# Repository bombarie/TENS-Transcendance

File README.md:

# TENS-Transcendance

Hardware design and code related to the development of a remotely-triggerable system of TENS muscle stimulation as part of the experimental dance / VR performance [Transcendance](https://www.theaterutrecht.nl/voorstellingen/transcendance).

The system extends an existing TENS muscle stimulator, the [Promed TENS 1000S](https://www.promed.de/soft-therapy/electrical-pain-therapy/144/promed-pain-therapy-device-tens-1000-s) and makes it controllable with OpenSoundControl (OSC) via WiFi through the use of an ESP32 microcontroller.

### Included in this repository 

**Software**
  - The [Arduino](https://www.arduino.cc/) code for the ESP32 microcontroller.
  - The code for the [Processing](https://processing.org/) sketch which served as a proxy between the ESP32 and a [TouchDesigner](https://derivative.ca/) patch (not by me) that was heavily integrating most of the performance.

**Hardware**
- The hardware designs to split a single TENS output channel to up to 16 different target locations. The PCB was designed in [KiCad](https://www.kicad.org/) 6.0.
- The additional libraries used in KiCad while designing the PCB are included in the repository.

### Dependencies

The software dependencies are enumerated in the Arduino and Processing folders.

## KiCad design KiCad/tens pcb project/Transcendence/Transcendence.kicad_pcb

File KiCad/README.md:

# KiCad designs

For this project we used a [Promed TENS 1000S](https://www.promed.de/soft-therapy/electrical-pain-therapy/144/promed-pain-therapy-device-tens-1000-s) TENS muscle stimulator, however there was a need to create multiple outputs, with these not needing to be active simultaneously. The TENS Output Board was designed in KiCad 6.x to support this use case. It houses a [CD74HC4067 16-channel multiplexer](https://www.sparkfun.com/products/9056) board and the switching is done using [Vishay VOR1142A6](https://www.digikey.com/en/products/detail/vishay-semiconductor-opto-division/VOR1142A6/6174564) mosfet relays.

Pressed for time the board was designed with ample room for further miniaturisation. Using solely through-hole components and spaced widely it has a distinctly oldschool look which I don't hate :)

### board layout

### 3d preview

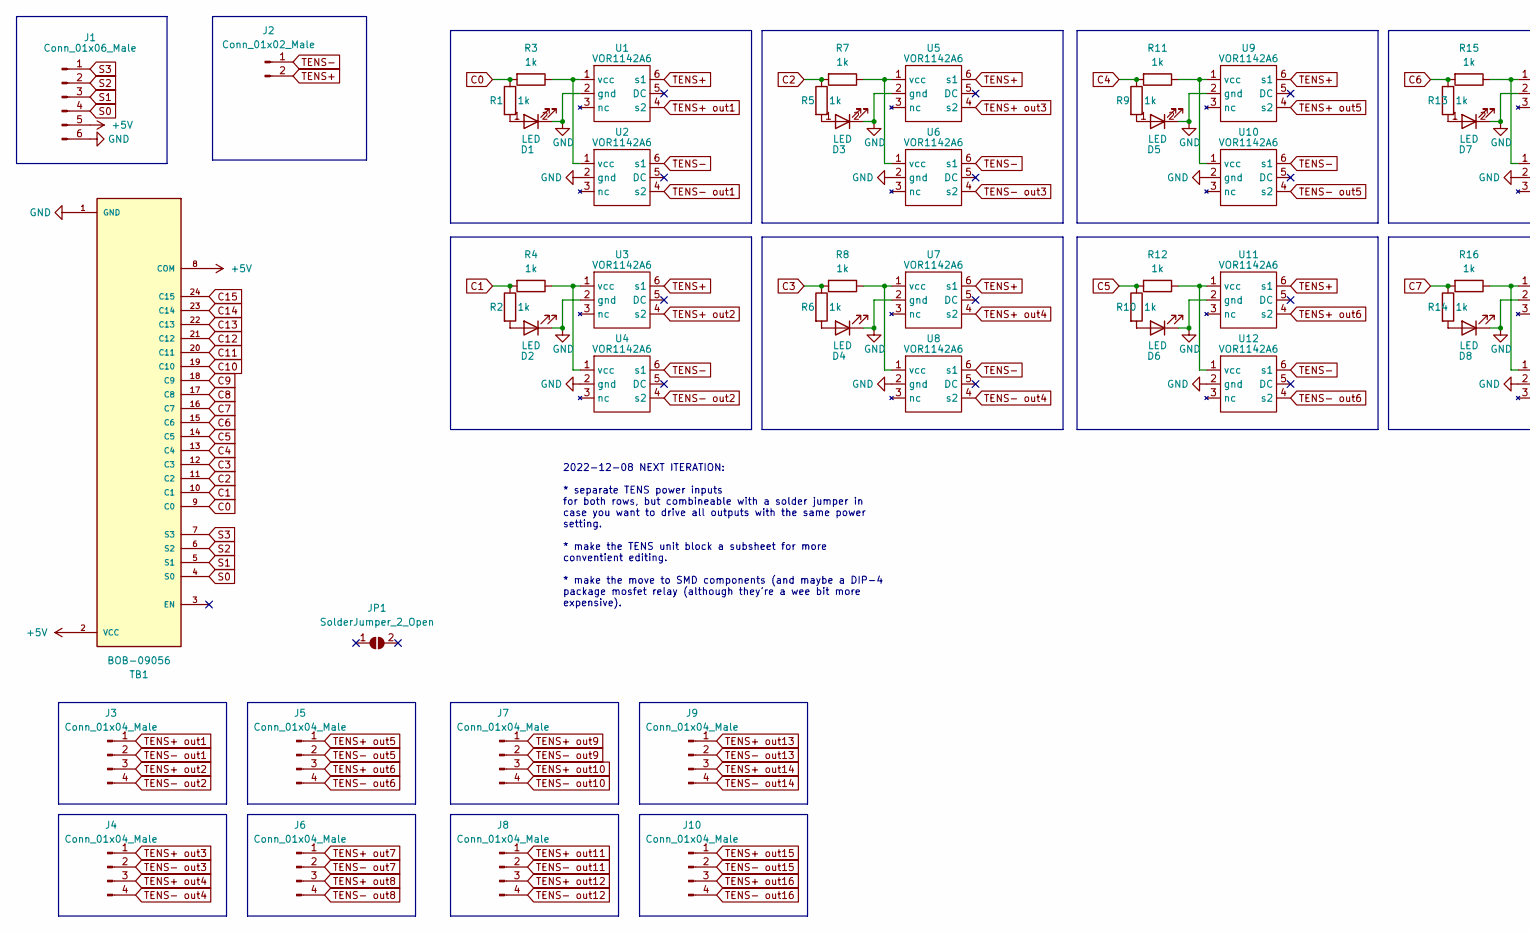
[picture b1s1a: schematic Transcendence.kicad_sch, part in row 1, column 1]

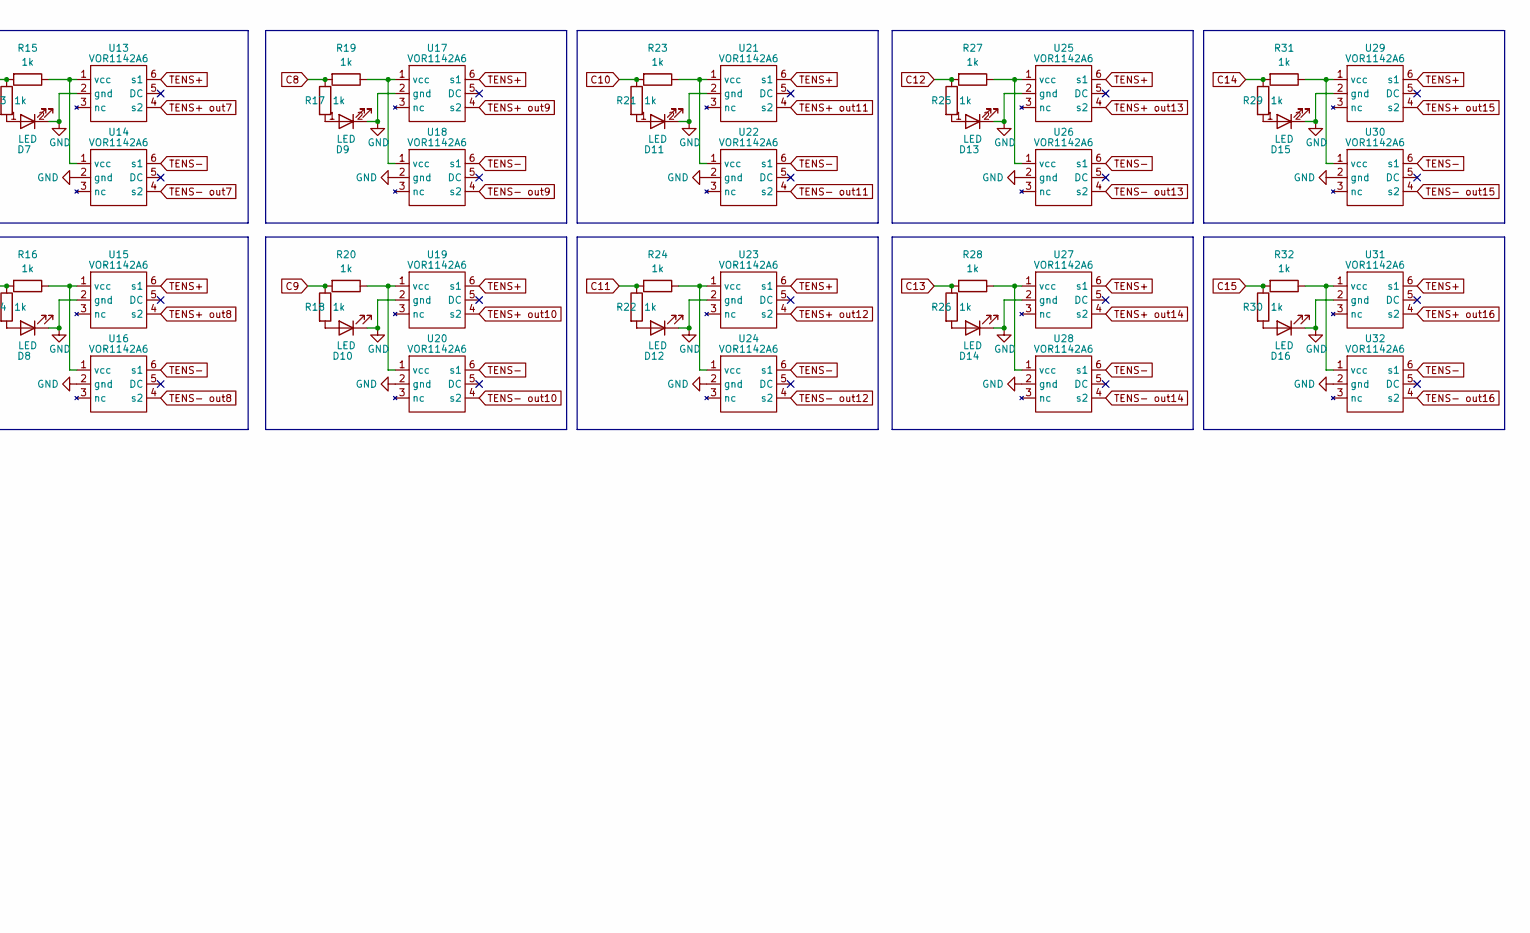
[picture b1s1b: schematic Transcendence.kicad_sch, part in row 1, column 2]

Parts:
D1, D2, D3, D4, D5, D6, D7, D8, D9, D10, D11, D12, D13, D14, D15, D16: LED; LED_D3.0mm
J1: Conn_01x06_Male; PinHeader_1x06_P2.54mm_Horizontal
J2: Conn_01x02_Male; PinHeader_1x02_P2.54mm_Horizontal
J3, J4, J5, J6, J7, J8, J9, J10: Conn_01x04_Male; PinHeader_1x04_P2.54mm_Horizontal
JP1: SolderJumper_2_Open; SolderJumper-2_P1.3mm_Open_Pad1.0x1.5mm
R1, R2, R3, R4, R5, R6, R7, R8, R9, R10, R11, R12, R13, R14, R15, R16, R17, R18, R19, R20, R21, R22, R23, R24, R25, R26, R27, R28, R29, R30, R31, R32: 1k; R_Axial_DIN0207_L6.3mm_D2.5mm_P2.54mm_Vertical
TB1: BOB-09056; XDCR_BOB-09056; PARTREV N/A
U1, U2, U3, U4, U5, U6, U7, U8, U9, U10, U11, U12, U13, U14, U15, U16, U17, U18, U19, U20, U21, U22, U23, U24, U25, U26, U27, U28, U29, U30, U31, U32: VOR1142A6; DIP-6_W7.62mm

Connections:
+5V: J1.5, TB1.2 (VCC), TB1.8 (COM)
C0: R1.1, R3.2, TB1.9 (C0)
C1: R2.1, R4.2, TB1.10 (C1)
C2: R5.1, R7.2, TB1.11 (C2)
C3: R6.1, R8.2, TB1.12 (C3)
C4: R9.1, R11.2, TB1.13 (C4)
C5: R10.1, R12.2, TB1.14 (C5)
C6: R13.1, R15.2, TB1.15 (C6)
C7: R14.1, R16.2, TB1.16 (C7)
C8: R17.1, R19.2, TB1.17 (C8)
C9: R18.1, R20.2, TB1.18 (C9)
C10: R21.1, R23.2, TB1.19 (C10)
C11: R22.1, R24.2, TB1.20 (C11)
C12: R25.1, R27.2, TB1.21 (C12)
C13: R26.1, R28.2, TB1.22 (C13)
C14: R29.1, R31.2, TB1.23 (C14)
C15: R30.1, R32.2, TB1.24 (C15)
GND: D1.2 (K), D2.2 (K), D3.2 (K), D4.2 (K), D5.2 (K), D6.2 (K), D7.2 (K), D8.2 (K), D9.2 (K), D10.2 (K), D11.2 (K), D12.2 (K), D13.2 (K), D14.2 (K), D15.2 (K), D16.2 (K), J1.6, TB1.1 (GND), U1.2 (gnd), U2.2 (gnd), U3.2 (gnd), U4.2 (gnd), U5.2 (gnd), U6.2 (gnd), U7.2 (gnd), U8.2 (gnd), U9.2 (gnd), U10.2 (gnd), U11.2 (gnd), U12.2 (gnd), U13.2 (gnd), U14.2 (gnd), U15.2 (gnd), U16.2 (gnd), U17.2 (gnd), U18.2 (gnd), U19.2 (gnd), U20.2 (gnd), U21.2 (gnd), U22.2 (gnd), U23.2 (gnd), U24.2 (gnd), U25.2 (gnd), U26.2 (gnd), U27.2 (gnd), U28.2 (gnd), U29.2 (gnd), U30.2 (gnd), U31.2 (gnd), U32.2 (gnd)
unnamed: D1.1 (A), R1.2
unnamed: D2.1 (A), R2.2
unnamed: D3.1 (A), R5.2
unnamed: D4.1 (A), R6.2
unnamed: D5.1 (A), R9.2
unnamed: D6.1 (A), R10.2
unnamed: D7.1 (A), R13.2
unnamed: D8.1 (A), R14.2
unnamed: D9.1 (A), R17.2
unnamed: D10.1 (A), R18.2
unnamed: D11.1 (A), R21.2
unnamed: D12.1 (A), R22.2
unnamed: D13.1 (A), R25.2
unnamed: D14.1 (A), R26.2
unnamed: D15.1 (A), R29.2
unnamed: D16.1 (A), R30.2
unnamed: R3.1, U1.1 (vcc), U2.1 (vcc)
unnamed: R4.1, U3.1 (vcc), U4.1 (vcc)
unnamed: R7.1, U5.1 (vcc), U6.1 (vcc)
unnamed: R8.1, U7.1 (vcc), U8.1 (vcc)
unnamed: R11.1, U9.1 (vcc), U10.1 (vcc)
unnamed: R12.1, U11.1 (vcc), U12.1 (vcc)
unnamed: R15.1, U13.1 (vcc), U14.1 (vcc)
unnamed: R16.1, U15.1 (vcc), U16.1 (vcc)
unnamed: R19.1, U17.1 (vcc), U18.1 (vcc)
unnamed: R20.1, U19.1 (vcc), U20.1 (vcc)
unnamed: R23.1, U21.1 (vcc), U22.1 (vcc)
unnamed: R24.1, U23.1 (vcc), U24.1 (vcc)
unnamed: R27.1, U25.1 (vcc), U26.1 (vcc)
unnamed: R28.1, U27.1 (vcc), U28.1 (vcc)
unnamed: R31.1, U29.1 (vcc), U30.1 (vcc)
unnamed: R32.1, U31.1 (vcc), U32.1 (vcc)
S0: J1.4, TB1.4 (S0)
S1: J1.3, TB1.5 (S1)
S2: J1.2, TB1.6 (S2)
S3: J1.1, TB1.7 (S3)
TENS+: J2.2, U1.6 (s1), U3.6 (s1), U5.6 (s1), U7.6 (s1), U9.6 (s1), U11.6 (s1), U13.6 (s1), U15.6 (s1), U17.6 (s1), U19.6 (s1), U21.6 (s1), U23.6 (s1), U25.6 (s1), U27.6 (s1), U29.6 (s1), U31.6 (s1)
TENS+ out1: J3.1, U1.4 (s2)
TENS+ out2: J3.3, U3.4 (s2)
TENS+ out3: J4.1, U5.4 (s2)
TENS+ out4: J4.3, U7.4 (s2)
TENS+ out5: J5.1, U9.4 (s2)
TENS+ out6: J5.3, U11.4 (s2)
TENS+ out7: J6.1, U13.4 (s2)
TENS+ out8: J6.3, U15.4 (s2)
TENS+ out9: J7.1, U17.4 (s2)
TENS+ out10: J7.3, U19.4 (s2)
TENS+ out11: J8.1, U21.4 (s2)
TENS+ out12: J8.3, U23.4 (s2)
TENS+ out13: J9.1, U25.4 (s2)
TENS+ out14: J9.3, U27.4 (s2)
TENS+ out15: J10.1, U29.4 (s2)
TENS+ out16: J10.3, U31.4 (s2)
TENS-: J2.1, U2.6 (s1), U4.6 (s1), U6.6 (s1), U8.6 (s1), U10.6 (s1), U12.6 (s1), U14.6 (s1), U16.6 (s1), U18.6 (s1), U20.6 (s1), U22.6 (s1), U24.6 (s1), U26.6 (s1), U28.6 (s1), U30.6 (s1), U32.6 (s1)
TENS- out1: J3.2, U2.4 (s2)
TENS- out2: J3.4, U4.4 (s2)
TENS- out3: J4.2, U6.4 (s2)
TENS- out4: J4.4, U8.4 (s2)
TENS- out5: J5.2, U10.4 (s2)
TENS- out6: J5.4, U12.4 (s2)
TENS- out7: J6.2, U14.4 (s2)
TENS- out8: J6.4, U16.4 (s2)
TENS- out9: J7.2, U18.4 (s2)
TENS- out10: J7.4, U20.4 (s2)
TENS- out11: J8.2, U22.4 (s2)
TENS- out12: J8.4, U24.4 (s2)
TENS- out13: J9.2, U26.4 (s2)
TENS- out14: J9.4, U28.4 (s2)
TENS- out15: J10.2, U30.4 (s2)
TENS- out16: J10.4, U32.4 (s2)

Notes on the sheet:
2022-12-08 NEXT ITERATION: * separate TENS power inputs for both rows, but combineable with a solder jumper in case you want to drive all outputs with the same power setting. * make the TENS unit block a subsheet for more conventient editing. * make the move to SMD components (and maybe a DIP-4 pac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

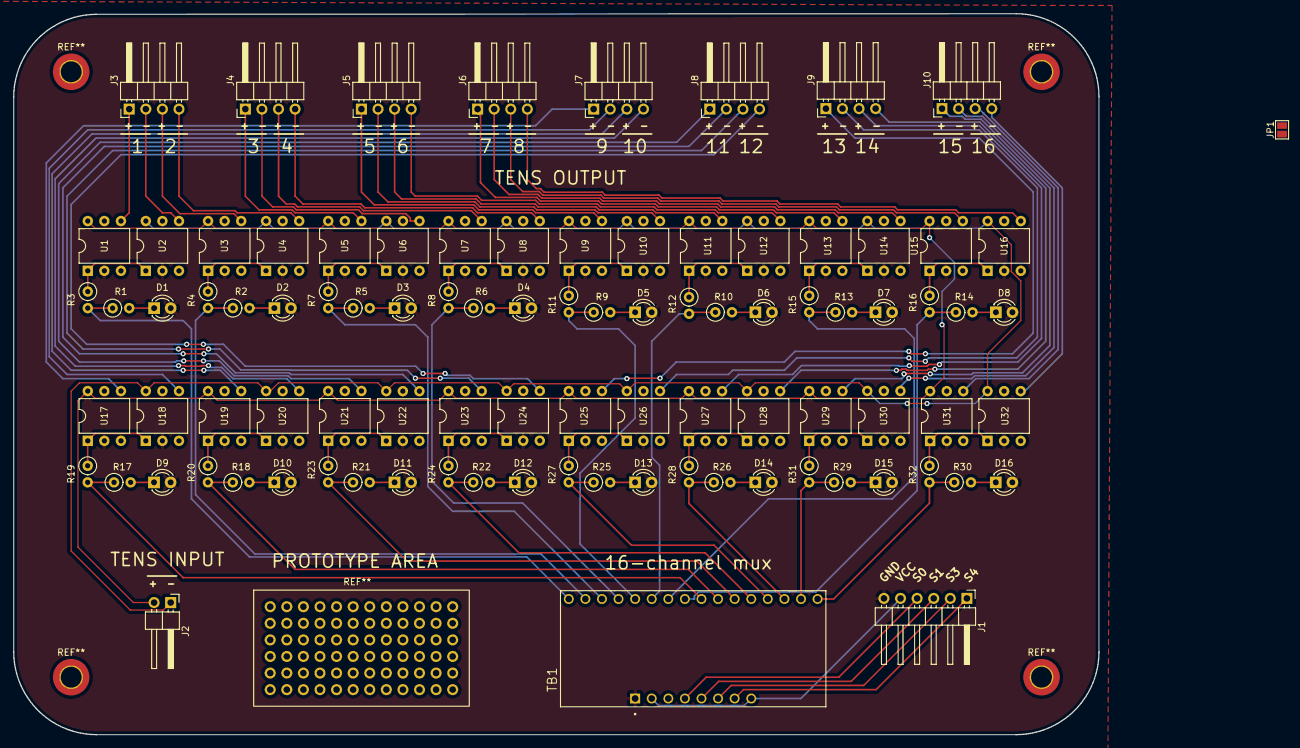
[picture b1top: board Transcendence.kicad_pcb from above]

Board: 2 copper layers, 166.2 x 110.4 mm, 92 parts (0 on the bottom side), 88 nets.

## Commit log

2022-12-21 Add Arduino sketches
2022-12-21 add. KiCad project
2022-12-21 add KiCad external and self-made libraries
2022-12-21 add Processing sketches
2022-12-22 bring wifi settings more to forefront
2022-12-22 add READMEs for Arduino and Processing sketches
    mainly intended to describe dependencies.
2022-12-28 add some readme files and descriptions
